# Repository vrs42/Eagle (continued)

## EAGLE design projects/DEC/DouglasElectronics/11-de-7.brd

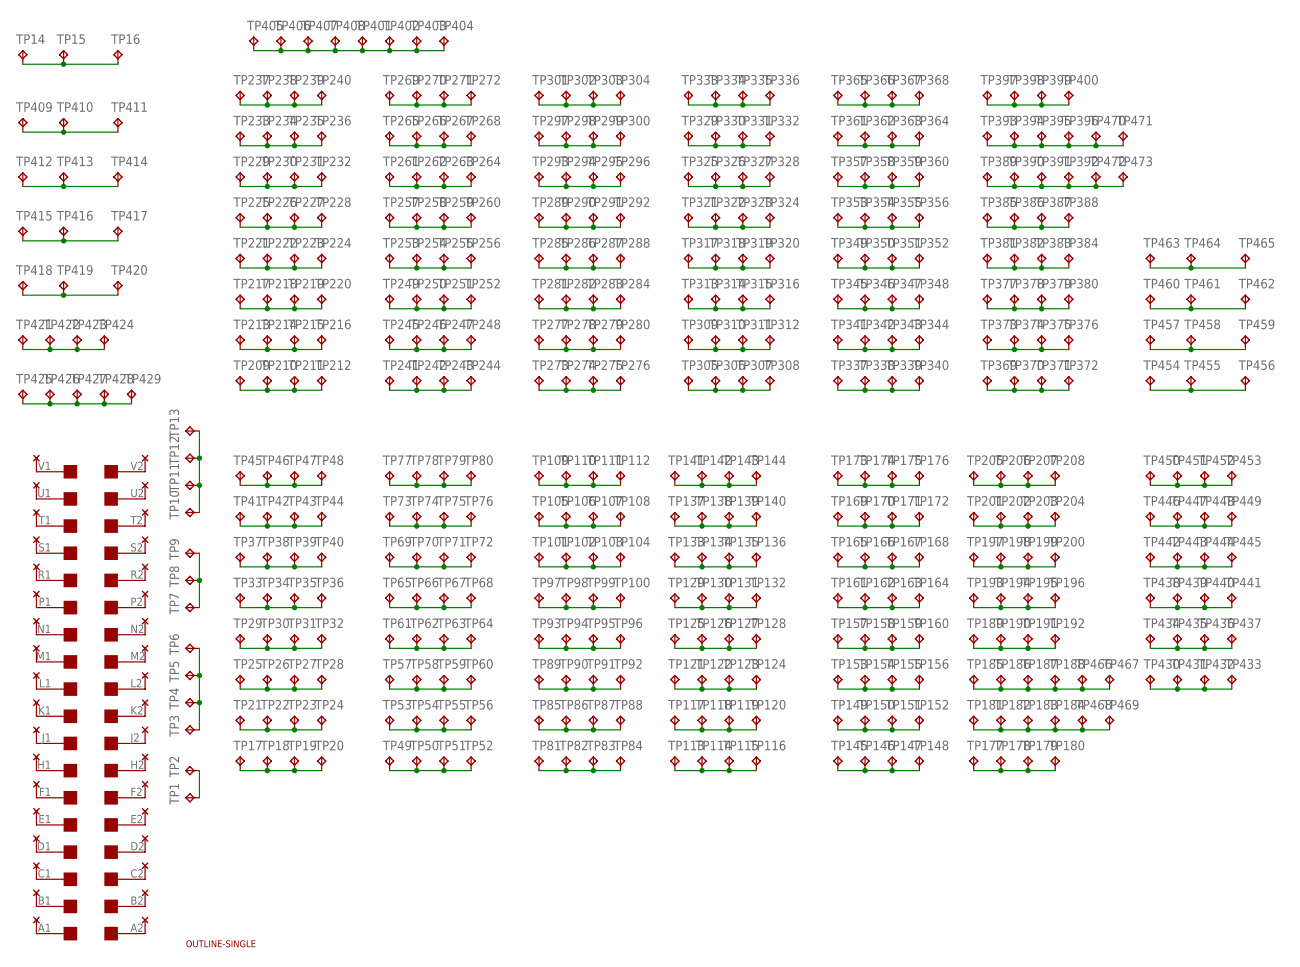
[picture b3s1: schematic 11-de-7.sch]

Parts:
TP1, TP3, TP4, TP5, TP6, TP7, TP8, TP9, TP10, TP11, TP12, TP13, TP14, TP15, TP16, TP17, TP18, TP19, TP20, TP21, TP22, TP23, TP24, TP25, TP26, TP27, TP28, TP29, TP30, TP31, TP32, TP33, TP34, TP35, TP36, TP37, TP38, TP39, TP40, TP41, TP42, TP43, TP44, TP45, TP46, TP47, TP48, TP49, TP50, TP51, TP52, TP53, TP54, TP55, TP56, TP57, TP58, TP59, TP60, TP61, TP62, TP63, TP64, TP65, TP66, TP67, TP68, TP69, TP70, TP71, TP72, TP73, TP74, TP75, TP76, TP77, TP78, TP79, TP80, TP81, TP82, TP83, TP84, TP85, TP86, TP87, TP88, TP89, TP90, TP91, TP92, TP93, TP94, TP95, TP96, TP97, TP98, TP99, TP100, TP101, TP102, TP103, TP104, TP105, TP106, TP107, TP108, TP109, TP110, TP111, TP112, TP113, TP114, TP115, TP116, TP117, TP118, TP119, TP120, TP121, TP122, TP123, TP124, TP125, TP126, TP127, TP128, TP129, TP130, TP131, TP132, TP133, TP134, TP135, TP136, TP137, TP138, TP139, TP140, TP141, TP142, TP143, TP144, TP145, TP146, TP147, TP148, TP149, TP150, TP151, TP152, TP153, TP154, TP155, TP156, TP157, TP158, TP159, TP160, TP161, TP162, TP163, TP164, TP165, TP166, TP167, TP168, TP169, TP170, TP171, TP172, TP173, TP174, TP175, TP176, TP177, TP178, TP179, TP180, TP181, TP182, TP183, TP184, TP185, TP186, TP187, TP188, TP189, TP190, TP191, TP192, TP193, TP194, TP195, TP196, TP197, TP198, TP199, TP200, TP201, TP202, TP203, TP204, TP205, TP206, TP207, TP208, TP209, TP210, TP211, TP212, TP213, TP214, TP215, TP216, TP217, TP218, TP219, TP220, TP221, TP222, TP223, TP224, TP225, TP226, TP227, TP228, TP229, TP230, TP231, TP232, TP233, TP234, TP235, TP236, TP237, TP238, TP239, TP240, TP241, TP242, TP243, TP244, TP245, TP246, TP247, TP248, TP249, TP250, TP251, TP252, TP253, TP254, TP255, TP256, TP257, TP258, TP259, TP260, TP261, TP262, TP263, TP264, TP265, TP266, TP267, TP268, TP269, TP270, TP271, TP272, TP273, TP274, TP275, TP276, TP277, TP278, TP279, TP280, TP281, TP282, TP283, TP284, TP285, TP286, TP287, TP288, TP289, TP290, TP291, TP292, TP293, TP294, TP295, TP296, TP297, TP298, TP299, TP300, TP301, TP302, TP303, TP304, TP305, TP306, TP307, TP308, TP309, TP310, TP311, TP312, TP313, TP314, TP315, TP316, TP317, TP318, TP319, TP320, TP321, TP322, TP323, TP324, TP325, TP326, TP327, TP328, TP329, TP330, TP331, TP332, TP333, TP334, TP335, TP336, TP337, TP338, TP339, TP340, TP341, TP342, TP343, TP344, TP345, TP346, TP347, TP348, TP349, TP350, TP351, TP352, TP353, TP354, TP355, TP356, TP357, TP358, TP359, TP360, TP361, TP362, TP363, TP364, TP365, TP366, TP367, TP368, TP369, TP370, TP371, TP372, TP373, TP374, TP375, TP376, TP377, TP378, TP379, TP380, TP381, TP382, TP383, TP384, TP385, TP386, TP387, TP388, TP389, TP390, TP391, TP392, TP393, TP394, TP395, TP396, TP397, TP398, TP399, TP400, TP401, TP402, TP403, TP404, TP405, TP406, TP407, TP408, TP409, TP410, TP411, TP412, TP413, TP414, TP415, TP416, TP417, TP418, TP419, TP420, TP421, TP422, TP423, TP424, TP425, TP426, TP427, TP428, TP429, TP430, TP431, TP432, TP433, TP434, TP435, TP436, TP437, TP438, TP439, TP440, TP441, TP442, TP443, TP444, TP445, TP446, TP447, TP448, TP449, TP450, TP451, TP452, TP453, TP454, TP455, TP456, TP457, TP458, TP459, TP460, TP461, TP462, TP463, TP464, TP465, TP466, TP467, TP468, TP469, TP470, TP471, TP472, TP473: TPPAD1-13Y; P1-13Y
TP2: TPPAD1-13; P1-13
U$1: SINGLE; EDGE-CON2
U$3: OUTLINE-SINGLE; SINGLE
U$5: THRU-HOLE2C; THRU-HOLEC

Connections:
unnamed: U$1.L2, U$5.L2
unnamed: U$1.M2, U$5.M2
unnamed: U$1.N2, U$5.N2
unnamed: U$1.K2, U$5.K2
unnamed: U$1.J2, U$5.J2
unnamed: U$1.H2, U$5.H2
unnamed: U$1.F2, U$5.F2
unnamed: U$1.P2, U$5.P2
unnamed: U$1.R2, U$5.R2
unnamed: U$1.S2, U$5.S2
unnamed: U$1.T2, U$5.T2
unnamed: U$1.E2, U$5.E2
unnamed: U$1.D2, U$5.D2
unnamed: U$1.U2, U$5.U2
unnamed: U$1.V2, U$5.V2
unnamed: U$1.C2, U$5.C2
unnamed: U$1.B2, U$5.B2
unnamed: U$1.A2, U$5.A2
unnamed: U$1.V1, U$5.V1
unnamed: U$1.A1, U$5.A1
unnamed: U$1.B1, U$5.B1
unnamed: U$1.C1, U$5.C1
unnamed: U$1.D1, U$5.D1
unnamed: U$1.E1, U$5.E1
unnamed: U$1.F1, U$5.F1
unnamed: U$1.H1, U$5.H1
unnamed: U$1.J1, U$5.J1
unnamed: U$1.K1, U$5.K1
unnamed: U$1.L1, U$5.L1
unnamed: U$1.M1, U$5.M1
unnamed: U$1.N1, U$5.N1
unnamed: U$1.P1, U$5.P1
unnamed: U$1.R1, U$5.R1
unnamed: U$1.S1, U$5.S1
unnamed: U$1.T1, U$5.T1
unnamed: U$1.U1, U$5.U1
unnamed: TP1.TP, TP2.TP
unnamed: TP3.TP, TP4.TP, TP5.TP, TP6.TP
unnamed: TP10.TP, TP11.TP, TP12.TP, TP13.TP
unnamed: TP7.TP, TP8.TP, TP9.TP
unnamed: TP14.TP, TP15.TP, TP16.TP
unnamed: TP17.TP, TP18.TP, TP19.TP, TP20.TP
unnamed: TP21.TP, TP22.TP, TP23.TP, TP24.TP
unnamed: TP25.TP, TP26.TP, TP27.TP, TP28.TP
unnamed: TP29.TP, TP30.TP, TP31.TP, TP32.TP
unnamed: TP33.TP, TP34.TP, TP35.TP, TP36.TP
unnamed: TP37.TP, TP38.TP, TP39.TP, TP40.TP
unnamed: TP41.TP, TP42.TP, TP43.TP, TP44.TP
unnamed: TP45.TP, TP46.TP, TP47.TP, TP48.TP
unnamed: TP49.TP, TP50.TP, TP51.TP, TP52.TP
unnamed: TP53.TP, TP54.TP, TP55.TP, TP56.TP
unnamed: TP57.TP, TP58.TP, TP59.TP, TP60.TP
unnamed: TP61.TP, TP62.TP, TP63.TP, TP64.TP
unnamed: TP65.TP, TP66.TP, TP67.TP, TP68.TP
unnamed: TP69.TP, TP70.TP, TP71.TP, TP72.TP
unnamed: TP73.TP, TP74.TP, TP75.TP, TP76.TP
unnamed: TP77.TP, TP78.TP, TP79.TP, TP80.TP
unnamed: TP81.TP, TP82.TP, TP83.TP, TP84.TP
unnamed: TP85.TP, TP86.TP, TP87.TP, TP88.TP
unnamed: TP89.TP, TP90.TP, TP91.TP, TP92.TP
unnamed: TP93.TP, TP94.TP, TP95.TP, TP96.TP
unnamed: TP97.TP, TP98.TP, TP99.TP, TP100.TP
unnamed: TP101.TP, TP102.TP, TP103.TP, TP104.TP
unnamed: TP105.TP, TP106.TP, TP107.TP, TP108.TP
unnamed: TP109.TP, TP110.TP, TP111.TP, TP112.TP
unnamed: TP113.TP, TP114.TP, TP115.TP, TP116.TP
unnamed: TP117.TP, TP118.TP, TP119.TP, TP120.TP
unnamed: TP121.TP, TP122.TP, TP123.TP, TP124.TP
unnamed: TP125.TP, TP126.TP, TP127.TP, TP128.TP
unnamed: TP129.TP, TP130.TP, TP131.TP, TP132.TP
unnamed: TP133.TP, TP134.TP, TP135.TP, TP136.TP
unnamed: TP137.TP, TP138.TP, TP139.TP, TP140.TP
unnamed: TP141.TP, TP142.TP, TP143.TP, TP144.TP
unnamed: TP145.TP, TP146.TP, TP147.TP, TP148.TP
unnamed: TP149.TP, TP150.TP, TP151.TP, TP152.TP
unnamed: TP153.TP, TP154.TP, TP155.TP, TP156.TP
unnamed: TP157.TP, TP158.TP, TP159.TP, TP160.TP
unnamed: TP161.TP, TP162.TP, TP163.TP, TP164.TP
unnamed: TP165.TP, TP166.TP, TP167.TP, TP168.TP
unnamed: TP169.TP, TP170.TP, TP171.TP, TP172.TP
unnamed: TP173.TP, TP174.TP, TP175.TP, TP176.TP
unnamed: TP177.TP, TP178.TP, TP179.TP, TP180.TP
unnamed: TP181.TP, TP182.TP, TP183.TP, TP184.TP, TP468.TP, TP469.TP
unnamed: TP185.TP, TP186.TP, TP187.TP, TP188.TP, TP466.TP, TP467.TP
unnamed: TP189.TP, TP190.TP, TP191.TP, TP192.TP
unnamed: TP193.TP, TP194.TP, TP195.TP, TP196.TP
unnamed: TP197.TP, TP198.TP, TP199.TP, TP200.TP
unnamed: TP201.TP, TP202.TP, TP203.TP, TP204.TP
unnamed: TP205.TP, TP206.TP, TP207.TP, TP208.TP
unnamed: TP209.TP, TP210.TP, TP211.TP, TP212.TP
unnamed: TP213.TP, TP214.TP, TP215.TP, TP216.TP
unnamed: TP217.TP, TP218.TP, TP219.TP, TP220.TP
unnamed: TP221.TP, TP222.TP, TP223.TP, TP224.TP
unnamed: TP225.TP, TP226.TP, TP227.TP, TP228.TP
unnamed: TP229.TP, TP230.TP, TP231.TP, TP232.TP
unnamed: TP233.TP, TP234.TP, TP235.TP, TP236.TP
unnamed: TP237.TP, TP238.TP, TP239.TP, TP240.TP
unnamed: TP241.TP, TP242.TP, TP243.TP, TP244.TP
unnamed: TP245.TP, TP246.TP, TP247.TP, TP248.TP
unnamed: TP249.TP, TP250.TP, TP251.TP, TP252.TP
unnamed: TP253.TP, TP254.TP, TP255.TP, TP256.TP
unnamed: TP257.TP, TP258.TP, TP259.TP, TP260.TP
unnamed: TP261.TP, TP262.TP, TP263.TP, TP264.TP
unnamed: TP265.TP, TP266.TP, TP267.TP, TP268.TP
unnamed: TP269.TP, TP270.TP, TP271.TP, TP272.TP
unnamed: TP273.TP, TP274.TP, TP275.TP, TP276.TP
unnamed: TP277.TP, TP278.TP, TP279.TP, TP280.TP
unnamed: TP281.TP, TP282.TP, TP283.TP, TP284.TP
unnamed: TP285.TP, TP286.TP, TP287.TP, TP288.TP
unnamed: TP289.TP, TP290.TP, TP291.TP, TP292.TP
unnamed: TP293.TP, TP294.TP, TP295.TP, TP296.TP
unnamed: TP297.TP, TP298.TP, TP299.TP, TP300.TP
unnamed: TP301.TP, TP302.TP, TP303.TP, TP304.TP
unnamed: TP305.TP, TP306.TP, TP307.TP, TP308.TP
unnamed: TP309.TP, TP310.TP, TP311.TP, TP312.TP
unnamed: TP313.TP, TP314.TP, TP315.TP, TP316.TP
unnamed: TP317.TP, TP318.TP, TP319.TP, TP320.TP
unnamed: TP321.TP, TP322.TP, TP323.TP, TP324.TP
unnamed: TP325.TP, TP326.TP, TP327.TP, TP328.TP
unnamed: TP329.TP, TP330.TP, TP331.TP, TP332.TP
unnamed: TP333.TP, TP334.TP, TP335.TP, TP336.TP
unnamed: TP337.TP, TP338.TP, TP339.TP, TP340.TP
unnamed: TP341.TP, TP342.TP, TP343.TP, TP344.TP
unnamed: TP345.TP, TP346.TP, TP347.TP, TP348.TP
unnamed: TP349.TP, TP350.TP, TP351.TP, TP352.TP
unnamed: TP353.TP, TP354.TP, TP355.TP, TP356.TP
unnamed: TP357.TP, TP358.TP, TP359.TP, TP360.TP
unnamed: TP361.TP, TP362.TP, TP363.TP, TP364.TP
unnamed: TP365.TP, TP366.TP, TP367.TP, TP368.TP
unnamed: TP369.TP, TP370.TP, TP371.TP, TP372.TP
unnamed: TP373.TP, TP374.TP, TP375.TP, TP376.TP
unnamed: TP377.TP, TP378.TP, TP379.TP, TP380.TP
unnamed: TP381.TP, TP382.TP, TP383.TP, TP384.TP
unnamed: TP385.TP, TP386.TP, TP387.TP, TP388.TP
unnamed: TP389.TP, TP390.TP, TP391.TP, TP392.TP, TP472.TP, TP473.TP
unnamed: TP393.TP, TP394.TP, TP395.TP, TP396.TP, TP470.TP, TP471.TP
unnamed: TP397.TP, TP398.TP, TP399.TP, TP400.TP
unnamed: TP401.TP, TP402.TP, TP403.TP, TP404.TP, TP405.TP, TP406.TP, TP407.TP, TP408.TP
unnamed: TP430.TP, TP431.TP, TP432.TP, TP433.TP
unnamed: TP434.TP, TP435.TP, TP436.TP, TP437.TP
unnamed: TP438.TP, TP439.TP, TP440.TP, TP441.TP
unnamed: TP442.TP, TP443.TP, TP444.TP, TP445.TP
unnamed: TP409.TP, TP410.TP, TP411.TP
unnamed: TP412.TP, TP413.TP, TP414.TP
unnamed: TP415.TP, TP416.TP, TP417.TP
unnamed: TP418.TP, TP419.TP, TP420.TP
unnamed: TP421.TP, TP422.TP, TP423.TP, TP424.TP
unnamed: TP425.TP, TP426.TP, TP427.TP, TP428.TP, TP429.TP
unnamed: TP446.TP, TP447.TP, TP448.TP, TP449.TP
unnamed: TP450.TP, TP451.TP, TP452.TP, TP453.TP
unnamed: TP454.TP, TP455.TP, TP456.TP
unnamed: TP457.TP, TP458.TP, TP459.TP
unnamed: TP460.TP, TP461.TP, TP462.TP
unnamed: TP463.TP, TP464.TP, TP465.TP

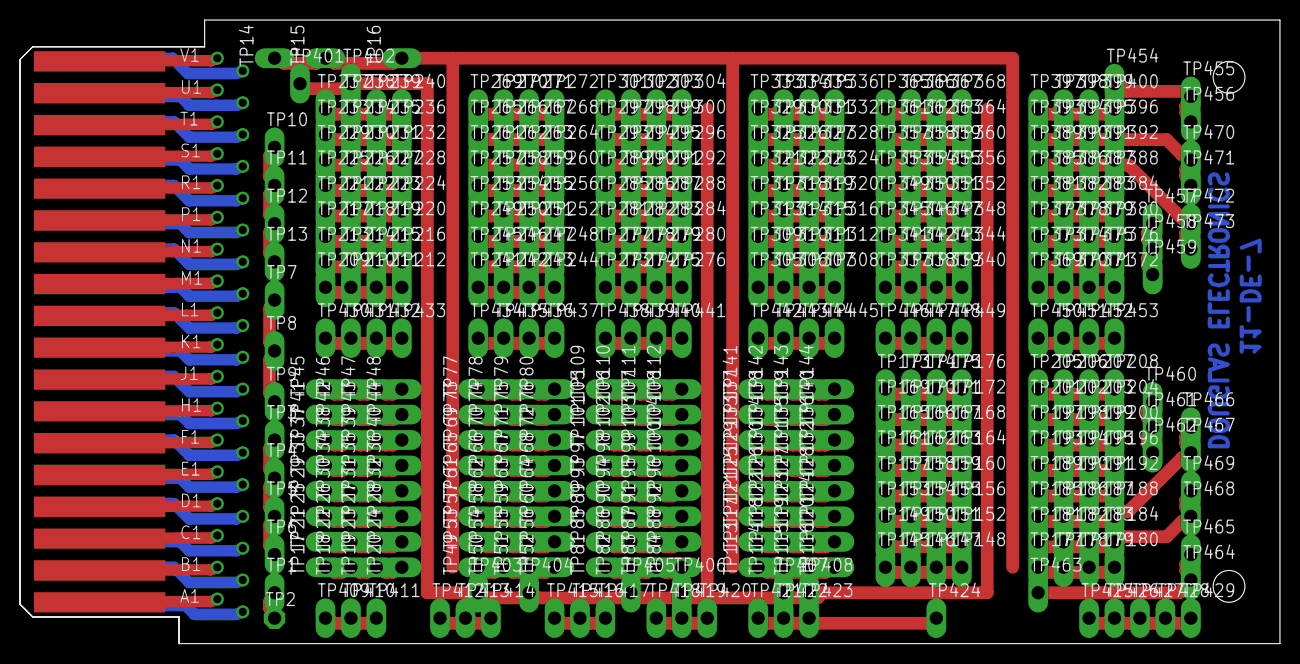
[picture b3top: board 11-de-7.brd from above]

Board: 2 copper layers, 125.7 x 62.2 mm, 476 parts (0 on the bottom side), 154 nets.

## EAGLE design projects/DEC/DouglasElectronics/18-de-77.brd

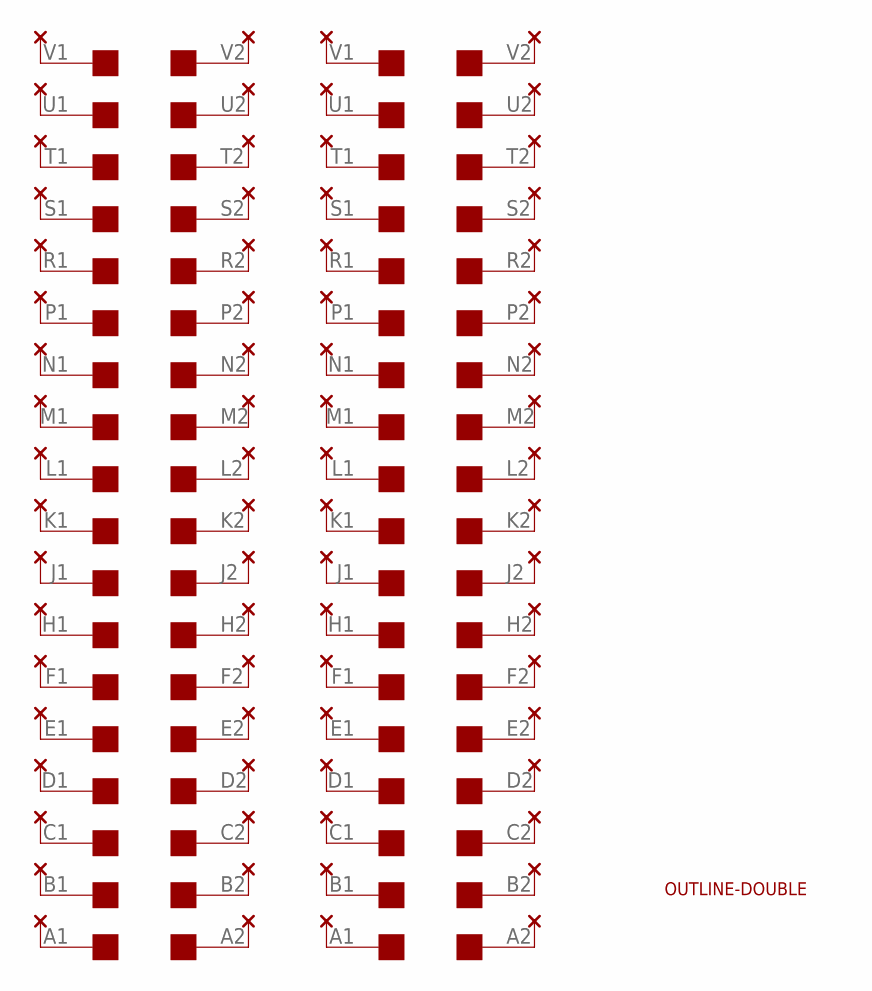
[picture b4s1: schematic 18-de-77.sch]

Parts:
U$1, U$6: SINGLE; EDGE-CON2
U$2, U$3: THRU-HOLE2A; THRU-HOLEA
U$4: OUTLINE-DOUBLE; DOUBLE

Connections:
unnamed: U$1.K2, U$2.K2
unnamed: U$1.J2, U$2.J2
unnamed: U$1.H2, U$2.H2
unnamed: U$1.L2, U$2.L2
unnamed: U$1.M2, U$2.M2
unnamed: U$1.N2, U$2.N2
unnamed: U$1.P2, U$2.P2
unnamed: U$1.F2, U$2.F2
unnamed: U$1.E2, U$2.E2
unnamed: U$1.D2, U$2.D2
unnamed: U$1.C2, U$2.C2
unnamed: U$1.R2, U$2.R2
unnamed: U$1.S2, U$2.S2
unnamed: U$1.B2, U$2.B2
unnamed: U$1.A2, U$2.A2
unnamed: U$1.T2, U$2.T2
unnamed: U$1.U2, U$2.U2
unnamed: U$1.V2, U$2.V2
unnamed: U$1.A1, U$2.A1
unnamed: U$1.V1, U$2.V1
unnamed: U$1.U1, U$2.U1
unnamed: U$1.T1, U$2.T1
unnamed: U$1.S1, U$2.S1
unnamed: U$1.R1, U$2.R1
unnamed: U$1.P1, U$2.P1
unnamed: U$1.N1, U$2.N1
unnamed: U$1.M1, U$2.M1
unnamed: U$1.L1, U$2.L1
unnamed: U$1.K1, U$2.K1
unnamed: U$1.J1, U$2.J1
unnamed: U$1.H1, U$2.H1
unnamed: U$1.F1, U$2.F1
unnamed: U$1.E1, U$2.E1
unnamed: U$1.D1, U$2.D1
unnamed: U$1.C1, U$2.C1
unnamed: U$1.B1, U$2.B1
unnamed: U$3.K2, U$6.K2
unnamed: U$3.J2, U$6.J2
unnamed: U$3.H2, U$6.H2
unnamed: U$3.L2, U$6.L2
unnamed: U$3.M2, U$6.M2
unnamed: U$3.N2, U$6.N2
unnamed: U$3.P2, U$6.P2
unnamed: U$3.F2, U$6.F2
unnamed: U$3.E2, U$6.E2
unnamed: U$3.D2, U$6.D2
unnamed: U$3.C2, U$6.C2
unnamed: U$3.R2, U$6.R2
unnamed: U$3.S2, U$6.S2
unnamed: U$3.B2, U$6.B2
unnamed: U$3.A2, U$6.A2
unnamed: U$3.T2, U$6.T2
unnamed: U$3.U2, U$6.U2
unnamed: U$3.V2, U$6.V2
unnamed: U$3.A1, U$6.A1
unnamed: U$3.V1, U$6.V1
unnamed: U$3.U1, U$6.U1
unnamed: U$3.T1, U$6.T1
unnamed: U$3.S1, U$6.S1
unnamed: U$3.R1, U$6.R1
unnamed: U$3.P1, U$6.P1
unnamed: U$3.N1, U$6.N1
unnamed: U$3.M1, U$6.M1
unnamed: U$3.L1, U$6.L1
unnamed: U$3.K1, U$6.K1
unnamed: U$3.J1, U$6.J1
unnamed: U$3.H1, U$6.H1
unnamed: U$3.F1, U$6.F1
unnamed: U$3.E1, U$6.E1
unnamed: U$3.D1, U$6.D1
unnamed: U$3.C1, U$6.C1
unnamed: U$3.B1, U$6.B1

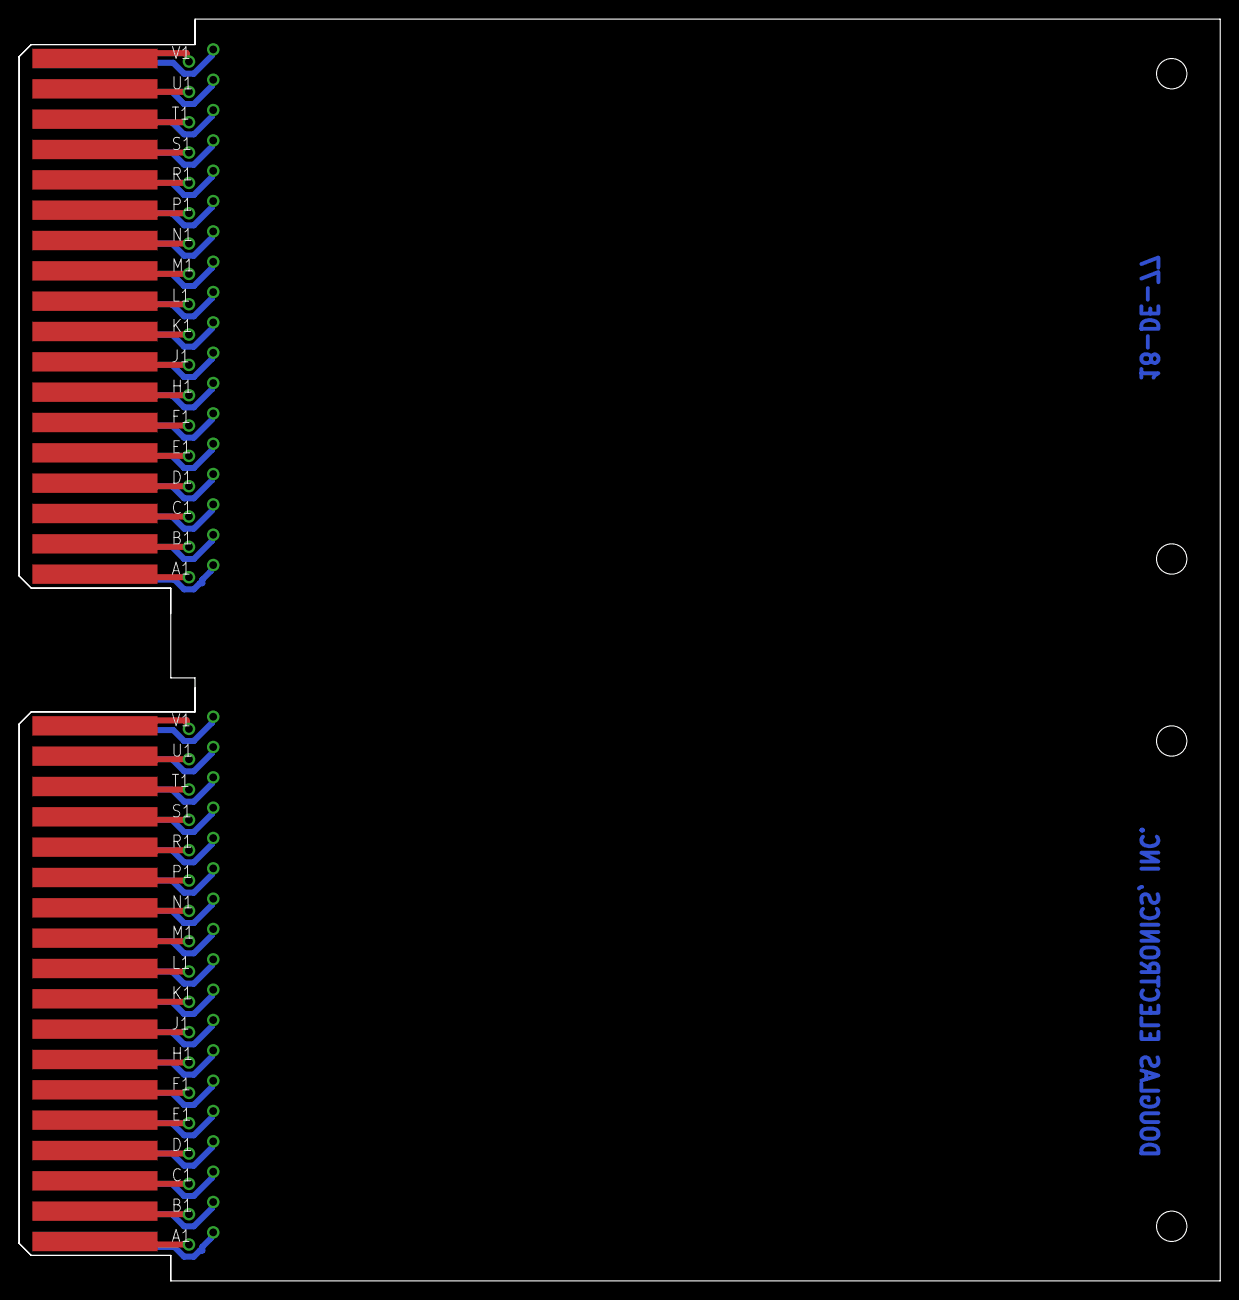
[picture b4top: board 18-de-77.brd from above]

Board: 2 copper layers, 125.7 x 132.1 mm, 5 parts (0 on the bottom side), 72 nets.

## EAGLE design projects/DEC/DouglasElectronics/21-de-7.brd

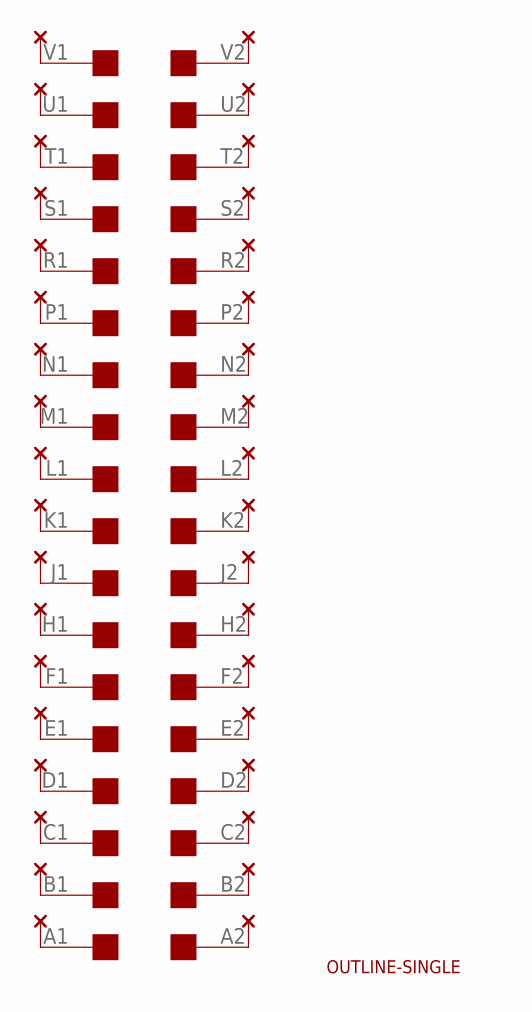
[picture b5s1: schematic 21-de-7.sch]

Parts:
U$1: SINGLE; EDGE-CON2
U$3: OUTLINE-SINGLE; SINGLE
U$4: THRU-HOLE2C; THRU-HOLEC

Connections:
unnamed: U$1.L2, U$4.L2
unnamed: U$1.M2, U$4.M2
unnamed: U$1.N2, U$4.N2
unnamed: U$1.K2, U$4.K2
unnamed: U$1.J2, U$4.J2
unnamed: U$1.H2, U$4.H2
unnamed: U$1.F2, U$4.F2
unnamed: U$1.P2, U$4.P2
unnamed: U$1.R2, U$4.R2
unnamed: U$1.S2, U$4.S2
unnamed: U$1.T2, U$4.T2
unnamed: U$1.E2, U$4.E2
unnamed: U$1.D2, U$4.D2
unnamed: U$1.U2, U$4.U2
unnamed: U$1.V2, U$4.V2
unnamed: U$1.C2, U$4.C2
unnamed: U$1.B2, U$4.B2
unnamed: U$1.A2, U$4.A2
unnamed: U$1.V1, U$4.V1
unnamed: U$1.A1, U$4.A1
unnamed: U$1.B1, U$4.B1
unnamed: U$1.C1, U$4.C1
unnamed: U$1.D1, U$4.D1
unnamed: U$1.E1, U$4.E1
unnamed: U$1.F1, U$4.F1
unnamed: U$1.H1, U$4.H1
unnamed: U$1.J1, U$4.J1
unnamed: U$1.K1, U$4.K1
unnamed: U$1.L1, U$4.L1
unnamed: U$1.M1, U$4.M1
unnamed: U$1.N1, U$4.N1
unnamed: U$1.P1, U$4.P1
unnamed: U$1.R1, U$4.R1
unnamed: U$1.S1, U$4.S1
unnamed: U$1.T1, U$4.T1
unnamed: U$1.U1, U$4.U1

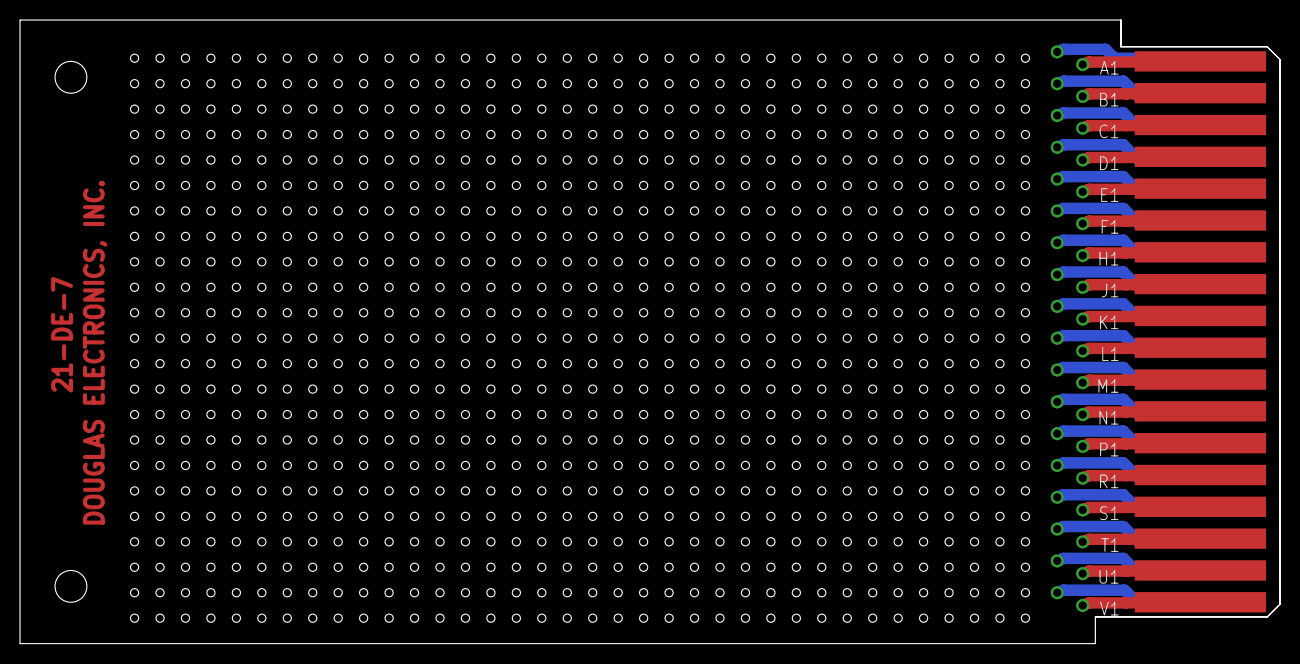
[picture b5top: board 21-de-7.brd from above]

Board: 2 copper layers, 125.7 x 62.2 mm, 3 parts (0 on the bottom side), 36 nets.

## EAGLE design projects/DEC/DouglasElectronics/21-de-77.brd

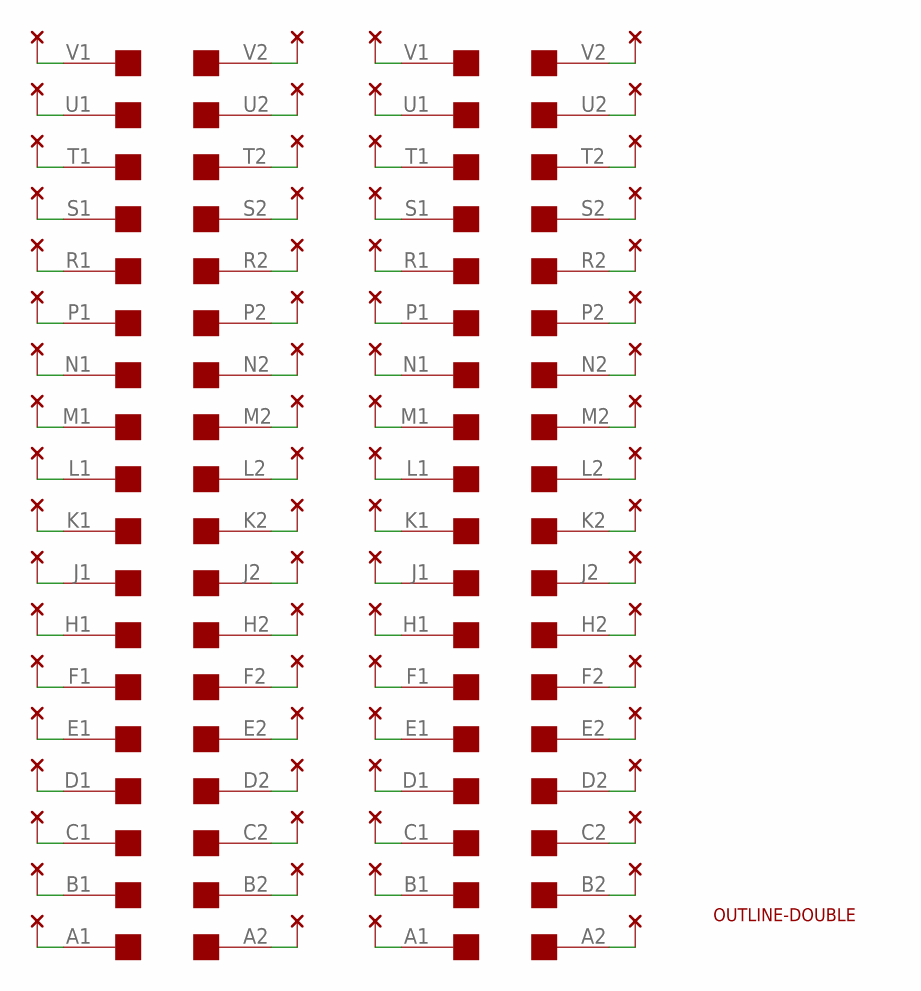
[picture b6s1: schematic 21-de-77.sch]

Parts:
U$1, U$6: SINGLE; EDGE-CON2
U$3, U$5: THRU-HOLE2C; THRU-HOLEC
U$4: OUTLINE-DOUBLE; DOUBLE

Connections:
unnamed: U$1.L2, U$3.L2
unnamed: U$1.M2, U$3.M2
unnamed: U$1.N2, U$3.N2
unnamed: U$1.K2, U$3.K2
unnamed: U$1.J2, U$3.J2
unnamed: U$1.H2, U$3.H2
unnamed: U$1.F2, U$3.F2
unnamed: U$1.P2, U$3.P2
unnamed: U$1.R2, U$3.R2
unnamed: U$1.S2, U$3.S2
unnamed: U$1.T2, U$3.T2
unnamed: U$1.E2, U$3.E2
unnamed: U$1.D2, U$3.D2
unnamed: U$1.U2, U$3.U2
unnamed: U$1.V2, U$3.V2
unnamed: U$1.C2, U$3.C2
unnamed: U$1.B2, U$3.B2
unnamed: U$1.A2, U$3.A2
unnamed: U$1.V1, U$3.V1
unnamed: U$1.A1, U$3.A1
unnamed: U$1.B1, U$3.B1
unnamed: U$1.C1, U$3.C1
unnamed: U$1.D1, U$3.D1
unnamed: U$1.E1, U$3.E1
unnamed: U$1.F1, U$3.F1
unnamed: U$1.H1, U$3.H1
unnamed: U$1.J1, U$3.J1
unnamed: U$1.K1, U$3.K1
unnamed: U$1.L1, U$3.L1
unnamed: U$1.M1, U$3.M1
unnamed: U$1.N1, U$3.N1
unnamed: U$1.P1, U$3.P1
unnamed: U$1.R1, U$3.R1
unnamed: U$1.S1, U$3.S1
unnamed: U$1.T1, U$3.T1
unnamed: U$1.U1, U$3.U1
unnamed: U$5.L2, U$6.L2
unnamed: U$5.M2, U$6.M2
unnamed: U$5.N2, U$6.N2
unnamed: U$5.K2, U$6.K2
unnamed: U$5.J2, U$6.J2
unnamed: U$5.H2, U$6.H2
unnamed: U$5.F2, U$6.F2
unnamed: U$5.P2, U$6.P2
unnamed: U$5.R2, U$6.R2
unnamed: U$5.S2, U$6.S2
unnamed: U$5.T2, U$6.T2
unnamed: U$5.E2, U$6.E2
unnamed: U$5.D2, U$6.D2
unnamed: U$5.U2, U$6.U2
unnamed: U$5.V2, U$6.V2
unnamed: U$5.C2, U$6.C2
unnamed: U$5.B2, U$6.B2
unnamed: U$5.A2, U$6.A2
unnamed: U$5.V1, U$6.V1
unnamed: U$5.A1, U$6.A1
unnamed: U$5.B1, U$6.B1
unnamed: U$5.C1, U$6.C1
unnamed: U$5.D1, U$6.D1
unnamed: U$5.E1, U$6.E1
unnamed: U$5.F1, U$6.F1
unnamed: U$5.H1, U$6.H1
unnamed: U$5.J1, U$6.J1
unnamed: U$5.K1, U$6.K1
unnamed: U$5.L1, U$6.L1
unnamed: U$5.M1, U$6.M1
unnamed: U$5.N1, U$6.N1
unnamed: U$5.P1, U$6.P1
unnamed: U$5.R1, U$6.R1
unnamed: U$5.S1, U$6.S1
unnamed: U$5.T1, U$6.T1
unnamed: U$5.U1, U$6.U1

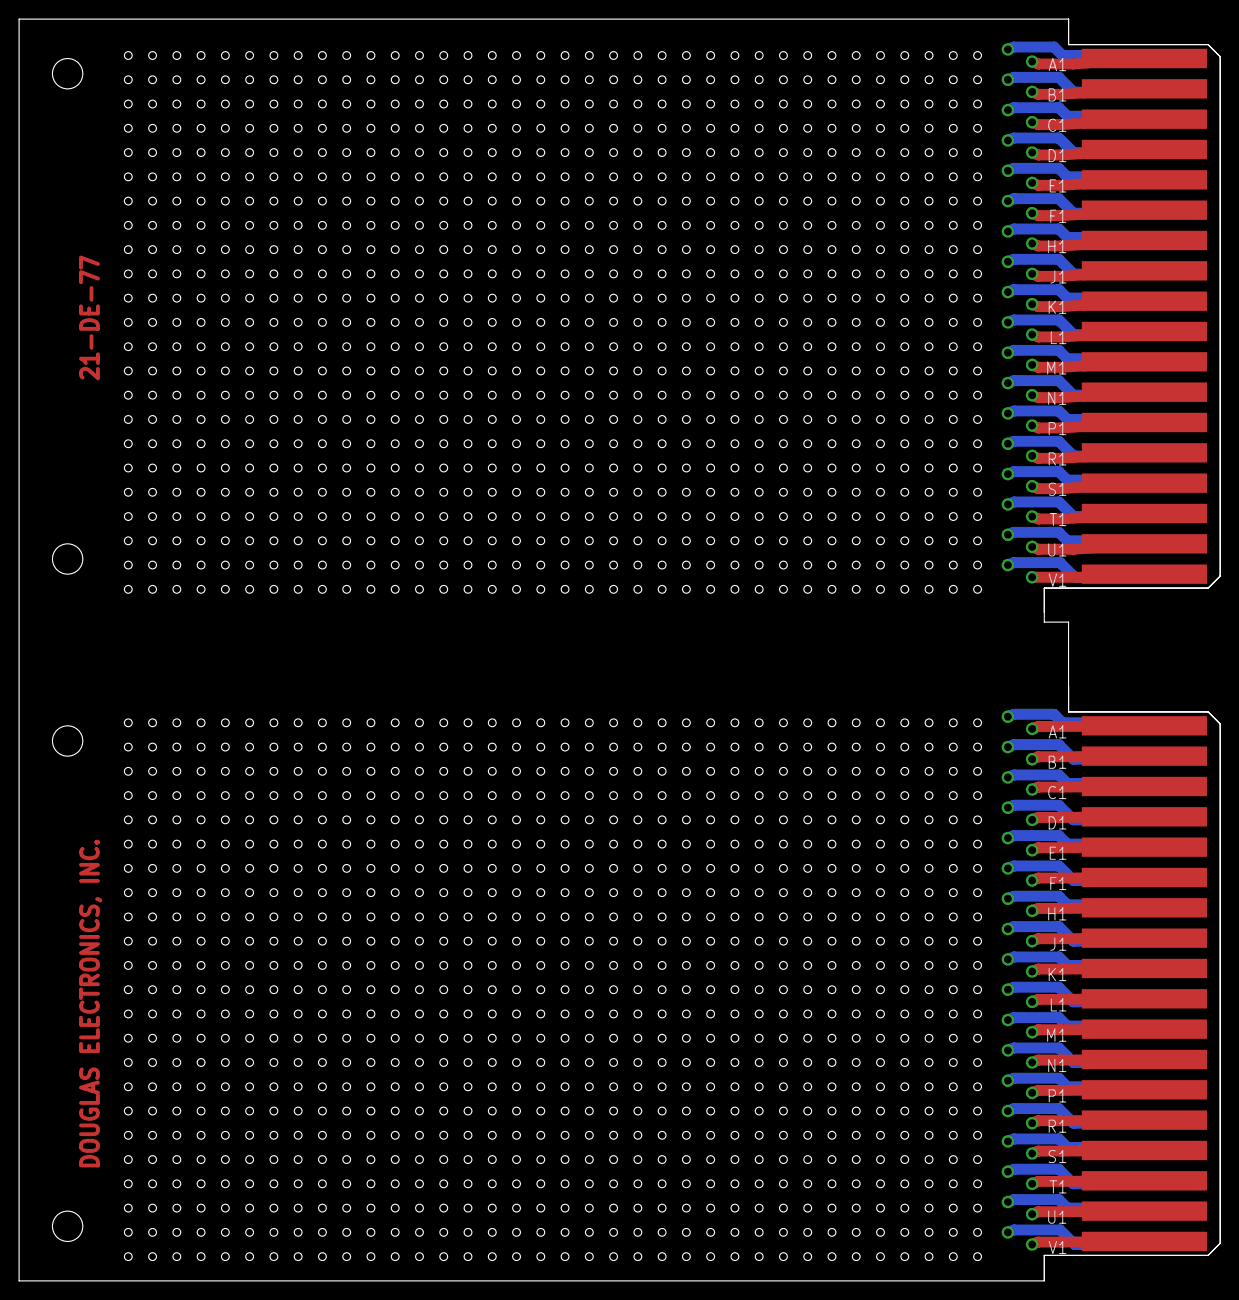
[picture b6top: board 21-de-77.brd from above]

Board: 2 copper layers, 125.7 x 132.1 mm, 5 parts (0 on the bottom side), 72 nets.
